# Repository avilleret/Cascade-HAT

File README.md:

% RPi B+ Hat

forked from : https://github.com/xesscorp/RPi_Hat_Template.git

Raspberry Pi B+ Hat
============================

Expansion Board
----------------------------

This is a project template for a 
[Raspberry Pi B+ Hat](https://github.com/raspberrypi/hats).

This base project includes a PCB edge defined according to 
[this specification](https://github.com/raspberrypi/hats/blob/master/hat-board-mechanical.pdf).
Both a thru-hole and a surface mount connector are provided, along with a different
PCB edge for each. Just keep the PCB edge and connector type that you're using for your design
and delete the others.

The component footprints used in this template are [here](https://github.com/xesscorp/RPi_Hat.pretty).

The board outline looks like this:

Using the Template
----------------------------

To use the Raspberry Pi Hat template with the through-hole connector, do the following:

1. Open the schematic. Remove the SMD connector, J1.
2. Generate the schematic netlist.
3. Generate the .cmp file. (The J2 connector will be the only component in it.)
4. Open the PCB. Hover your mouse over the connector and hit **e** to edit it. Select the J1 SMD connector. In the **Move and Place** section of the **Footprint Properties** window, select the **Free** radio button. Then click **OK**. The SMD connector should now be unlocked so it can be removed.
5. Read in the netlist from the schematic. In the **Extra Footprints** section of the **Netlist** dialog window, select the **Delete** radio button. Then click **Read Current Netlist**. The J1 SMD connector should disappear. Then click **Close**.
6. Finally, delete the upper two arcs and the edge of the board outline.

To use the Raspberry Pi Hat template with the SMD connector, do the following:

1. Open the schematic. Remove the through-hole connector, J2.
2. Generate the schematic netlist.
3. Generate the .cmp file. (The J1 connector will be the only component in it.)
4. Open the PCB. Hover your mouse over the connector and hit **e** to edit it. Select the J2 through-hole connector. In the **Move and Place** section of the **Footprint Properties** window, select the **Free** radio button. Then click **OK**. The through-hole connector should now be unlocked so it can be removed.
5. Read in the netlist from the schematic. In the **Extra Footprints** section of the **Netlist** dialog window, select the **Delete** radio button. Then click **Read Current Netlist**. The J2 through-hole connector should disappear. Then click **Close**.
6. Finally, delete the lower two arcs and the edge of the board outline.

(c)2015 XESS Corp.

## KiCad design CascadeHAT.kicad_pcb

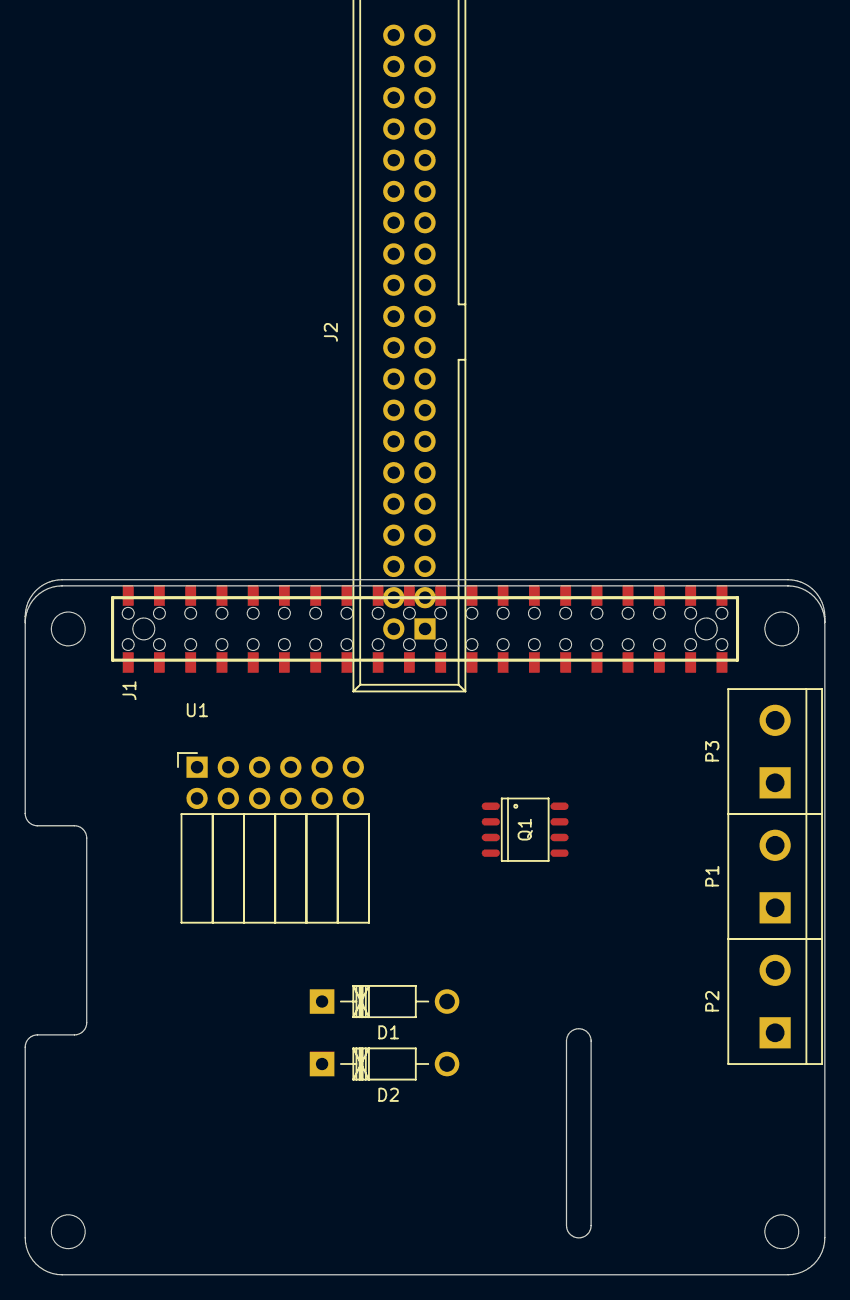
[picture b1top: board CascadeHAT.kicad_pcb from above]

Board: 2 copper layers, 65.0 x 56.5 mm, 9 parts (0 on the bottom side), 9 nets, no tracks yet.

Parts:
D1, D2: DIODE; Diode_DO-41_SOD81_Horizontal_RM10
J1: RPi_GPIO; Samtec_HLE-120-02-XXX-DV-BE-XX-XX
J2: RPi_GPIO; IDC_Header_Straight_40pins
P1, P2, P3: CONN_01X02; bornier2
Q1: FDS6898A; SO-8
U1: TC4427; Socket_Strip_Angled_2x06

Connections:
+5V: J2.2, J2.4, U1.6
GND: J2.6, J2.9, J2.14, J2.20, J2.25, J2.30, J2.34, J2.39, P3.2, Q1.5, Q1.8, U1.3
unnamed: P1.1, Q1.1
unnamed: P2.1, Q1.3
unnamed: J2.16, U1.2
unnamed: J2.18, U1.4
unnamed: Q1.2, U1.7
unnamed: Q1.4, U1.5
VDD: P1.2, P2.2, P3.1

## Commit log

2016-10-31 add fork reference
